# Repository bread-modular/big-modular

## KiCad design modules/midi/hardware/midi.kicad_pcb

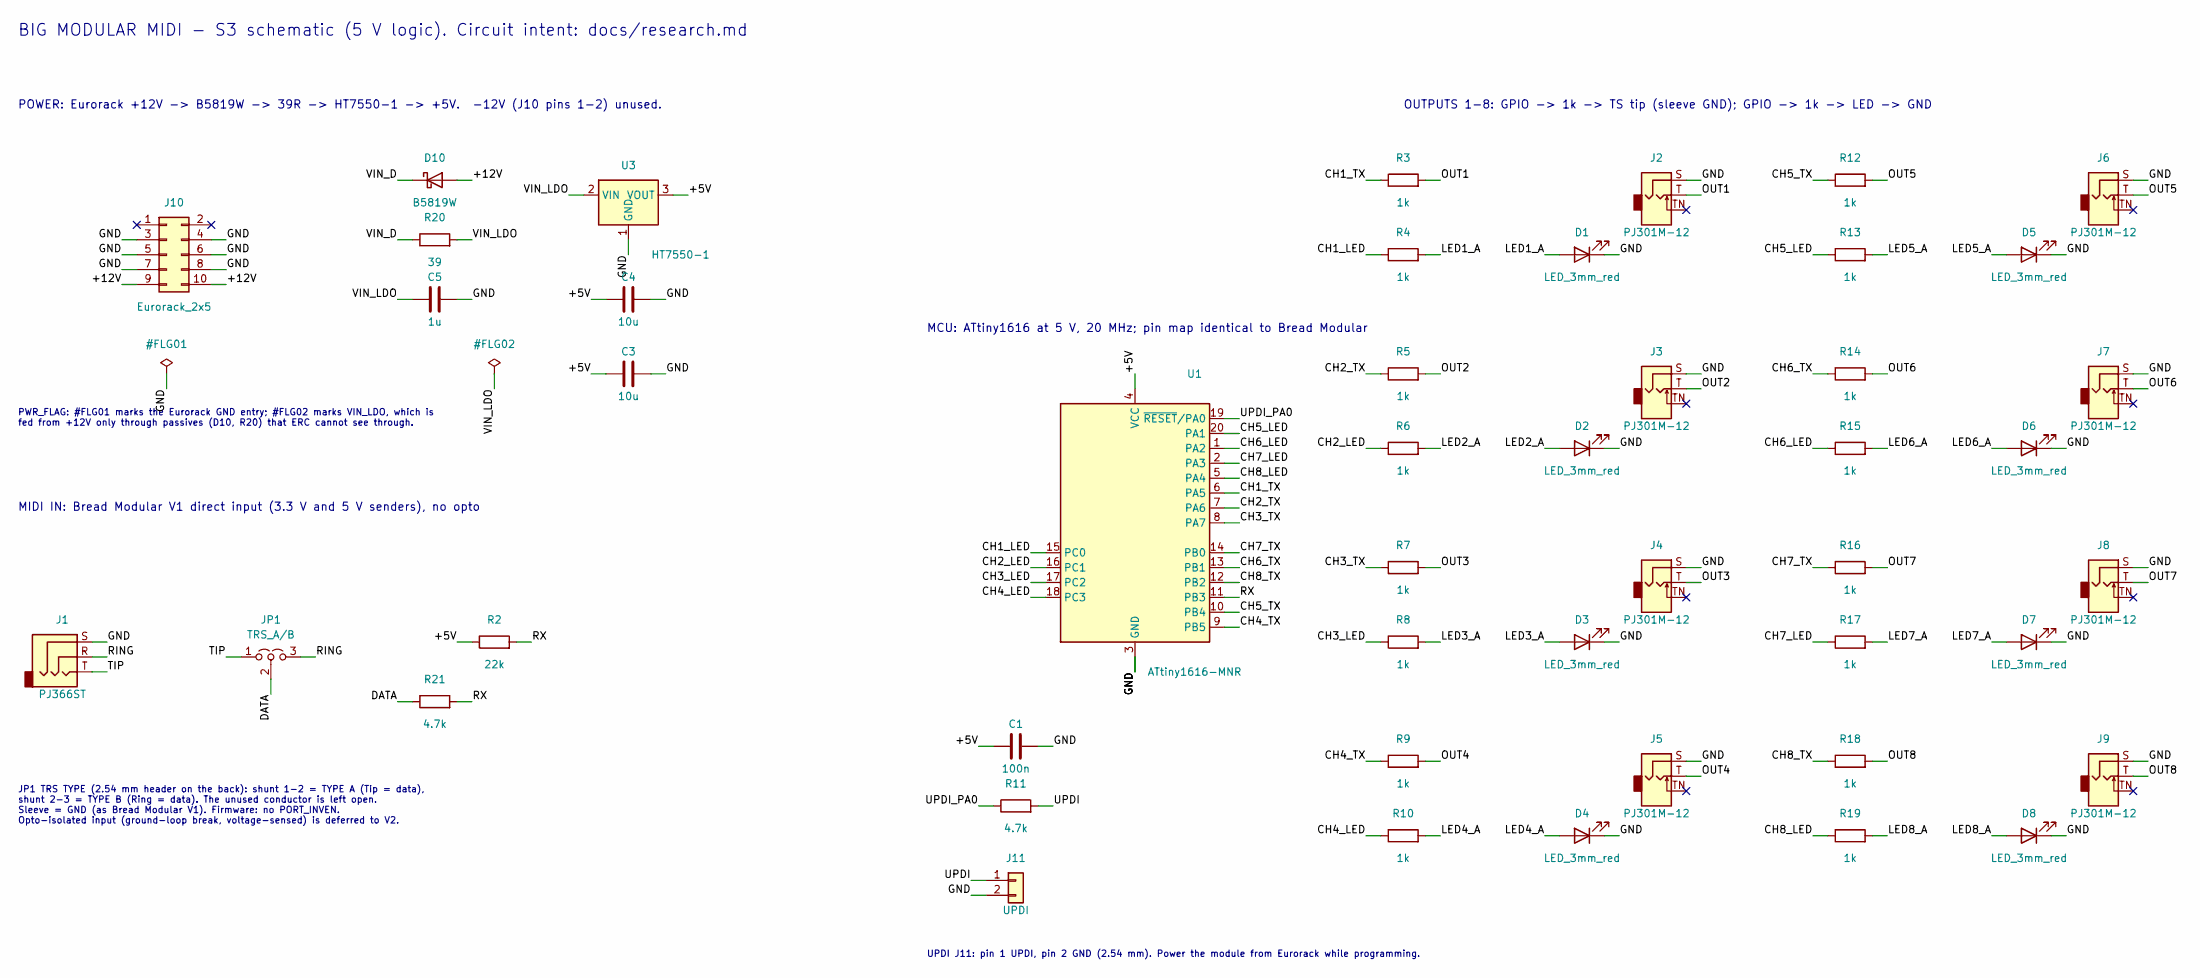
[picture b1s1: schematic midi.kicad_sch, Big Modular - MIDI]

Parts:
C1: 100n; C_0603_1608Metric; Voltage 50V; MPN CC0603KRX7R9BB104; LCSC C14663
C3, C4: 10u; C_0805_2012Metric; Voltage 25V; MPN CL21A106KAYNNNE; LCSC C15850
C5: 1u; C_0805_2012Metric; Voltage 50V; MPN CL21B105KBFNNNE; LCSC C28323
D1, D2, D3, D4, D5, D6, D7, D8: LED_3mm_red; LED_D3.0mm
D10: B5819W; D_SOD-123; MPN B5819W SL; LCSC C8598
J1: PJ366ST; Jack_3.5mm_QingPu_WQP-PJ366ST_Vertical
J2, J3, J4, J5, J6, J7, J8, J9: PJ301M-12; Jack_3.5mm_QingPu_WQP-PJ301M-12_Vertical
J10: Eurorack_2x5; PinHeader_2x05_P2.54mm_Vertical
J11: UPDI; PinHeader_1x02_P2.54mm_Vertical
JP1: TRS_A/B; PinHeader_1x03_P2.54mm_Vertical
R2: 22k; R_0603_1608Metric; MPN 0603WAF2202T5E; LCSC C31850
R3, R4, R5, R6, R7, R8, R9, R10, R12, R13, R14, R15, R16, R17, R18, R19: 1k; R_0603_1608Metric; MPN 0603WAF1001T5E; LCSC C21190
R11, R21: 4.7k; R_0603_1608Metric; MPN 0603WAF4701T5E; LCSC C23162
R20: 39; R_1206_3216Metric; MPN HP06W2F390JT5E; LCSC C414944
U1: ATtiny1616-MNR; VQFN-20-1EP_3x3mm_P0.4mm_EP1.7x1.7mm; MPN ATTINY1616-MNR; LCSC C507118
U3: HT7550-1; SOT-89-3; MPN HT7550-1; LCSC C16106

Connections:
/+5V: C1.1, C3.1, C4.1, R2.1, U1.4 (VCC), U3.3 (VOUT)
/+12V: D10.2 (A), J10.9, J10.10
/CH1_LED: R4.1, U1.15 (PC0)
/CH1_TX: R3.1, U1.6 (PA5)
/CH2_LED: R6.1, U1.16 (PC1)
/CH2_TX: R5.1, U1.7 (PA6)
/CH3_LED: R8.1, U1.17 (PC2)
/CH3_TX: R7.1, U1.8 (PA7)
/CH4_LED: R10.1, U1.18 (PC3)
/CH4_TX: R9.1, U1.9 (PB5)
/CH5_LED: R13.1, U1.20 (PA1)
/CH5_TX: R12.1, U1.10 (PB4)
/CH6_LED: R15.1, U1.1 (PA2)
/CH6_TX: R14.1, U1.13 (PB1)
/CH7_LED: R17.1, U1.2 (PA3)
/CH7_TX: R16.1, U1.14 (PB0)
/CH8_LED: R19.1, U1.5 (PA4)
/CH8_TX: R18.1, U1.12 (PB2)
/DATA: JP1.2 (C), R21.1
/GND: C1.2, C3.2, C4.2, C5.2, D1.1 (K), D2.1 (K), D3.1 (K), D4.1 (K), D5.1 (K), D6.1 (K), D7.1 (K), D8.1 (K), J1.S, J2.S, J3.S, J4.S, J5.S, J6.S, J7.S, J8.S, J9.S, J10.3, J10.4, J10.5, J10.6, J10.7, J10.8, J11.2, U1.3 (GND), U1.21 (GND), U3.1 (GND)
/LED1_A: D1.2 (A), R4.2
/LED2_A: D2.2 (A), R6.2
/LED3_A: D3.2 (A), R8.2
/LED4_A: D4.2 (A), R10.2
/LED5_A: D5.2 (A), R13.2
/LED6_A: D6.2 (A), R15.2
/LED7_A: D7.2 (A), R17.2
/LED8_A: D8.2 (A), R19.2
/OUT1: J2.T, R3.2
/OUT2: J3.T, R5.2
/OUT3: J4.T, R7.2
/OUT4: J5.T, R9.2
/OUT5: J6.T, R12.2
/OUT6: J7.T, R14.2
/OUT7: J8.T, R16.2
/OUT8: J9.T, R18.2
/RING: J1.R, JP1.3 (B)
/RX: R2.2, R21.2, U1.11 (PB3)
/TIP: J1.T, JP1.1 (A)
/UPDI: J11.1, R11.2
/UPDI_PA0: R11.1, U1.19 (~RESET/PA0)
/VIN_D: D10.1 (K), R20.1
/VIN_LDO: C5.1, R20.2, U3.2 (VIN)

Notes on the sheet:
JP1 TRS TYPE (2.54 mm header on the back): shunt 1-2 = TYPE A (Tip = data), shunt 2-3 = TYPE B (Ring = data). The unused conductor is left open. Sleeve = GND (as Bread Modular V1). Firmware: no PORT_INVEN. Opto-isolated input (ground-loop break, voltage-sensed) is deferred to V2.
MIDI IN: Bread Modular V1 direct input (3.3 V and 5 V senders), no opto
OUTPUTS 1-8: GPIO -> 1k -> TS tip (sleeve GND); GPIO -> 1k -> LED -> GND
PWR_FLAG: #FLG01 marks the Eurorack GND entry; #FLG02 marks VIN_LDO, which is fed from +12V only through passives (D10, R20) that ERC cannot see through.
POWER: Eurorack +12V -> B5819W -> 39R -> HT7550-1 -> +5V. -12V (J10 pins 1-2) unused.
BIG MODULAR MIDI - S3 schematic (5 V logic). Circuit intent: docs/research.md
UPDI J11: pin 1 UPDI, pin 2 GND (2.54 mm). Power the module from Eurorack while programming.
MCU: ATtiny1616 at 5 V, 20 MHz; pin map identical to Bread Modular

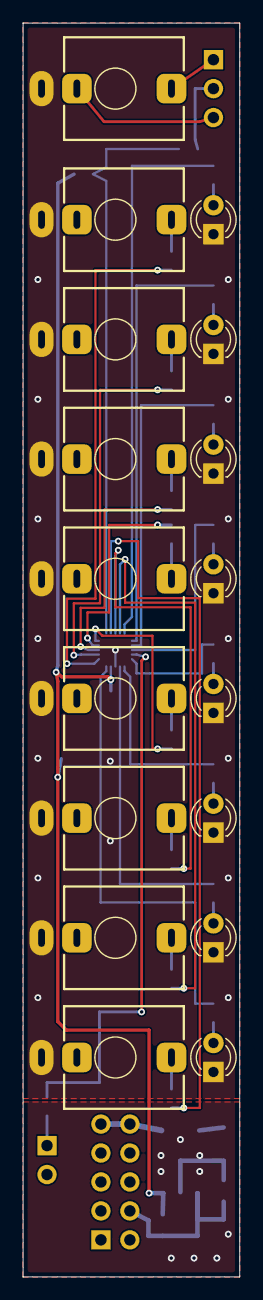
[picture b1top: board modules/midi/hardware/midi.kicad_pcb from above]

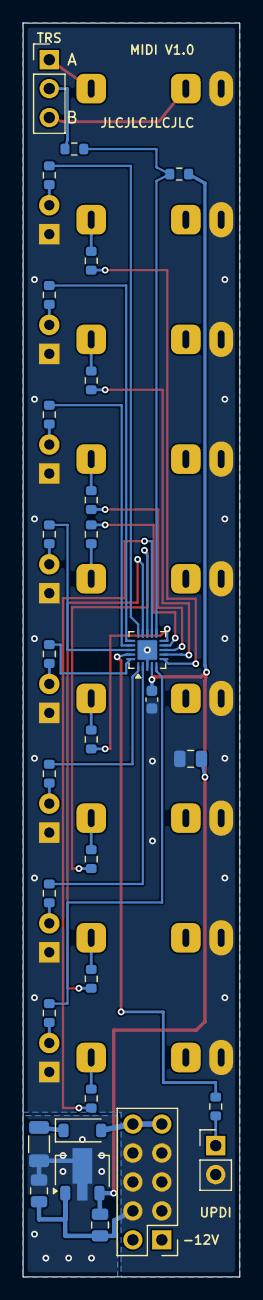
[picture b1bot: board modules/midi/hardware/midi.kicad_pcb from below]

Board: 2 copper layers, 19.0 x 110.0 mm, 47 parts (30 on the bottom side), 43 nets.

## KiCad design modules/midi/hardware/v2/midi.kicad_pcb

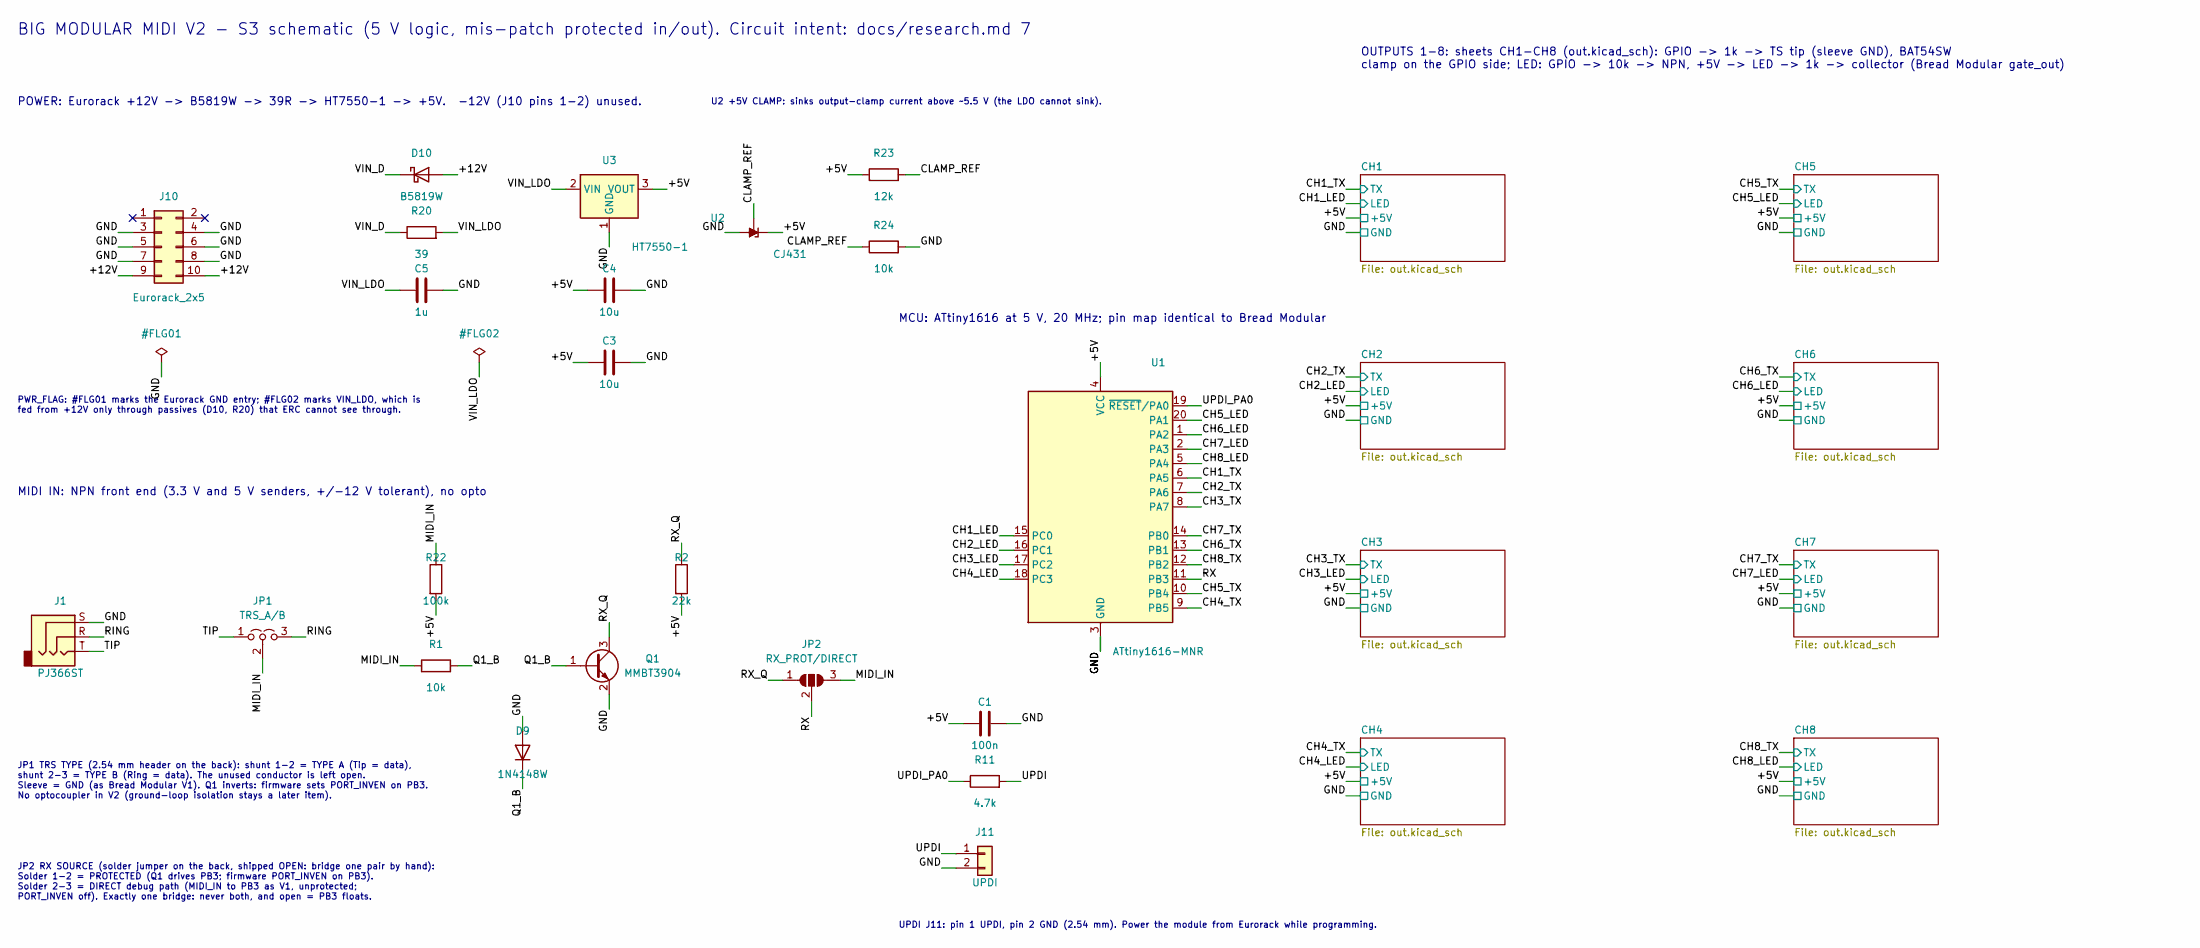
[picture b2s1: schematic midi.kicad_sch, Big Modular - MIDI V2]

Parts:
C1: 100n; C_0603_1608Metric; Voltage 50V; MPN CC0603KRX7R9BB104; LCSC C14663
C3, C4: 10u; C_0805_2012Metric; Voltage 25V; MPN CL21A106KAYNNNE; LCSC C15850
C5: 1u; C_0805_2012Metric; Voltage 50V; MPN CL21B105KBFNNNE; LCSC C28323
D9: 1N4148W; D_SOD-123; MPN 1N4148W; LCSC C81598
D10: B5819W; D_SOD-123; MPN B5819W SL; LCSC C8598
J1: PJ366ST; Jack_3.5mm_QingPu_WQP-PJ366ST_Vertical
J10: Eurorack_2x5; PinHeader_2x05_P2.54mm_Vertical
J11: UPDI; PinHeader_1x02_P2.54mm_Vertical
JP1: TRS_A/B; PinHeader_1x03_P2.54mm_Vertical
JP2: RX_PROT/DIRECT; SolderJumper-3_P1.3mm_Open_RoundedPad1.0x1.5mm
Q1: MMBT3904; SOT-23; MPN MMBT3904(RANGE:100-300); LCSC C20526
R1, R24: 10k; R_0603_1608Metric; MPN 0603WAF1002T5E; LCSC C25804
R2: 22k; R_0603_1608Metric; MPN 0603WAF2202T5E; LCSC C31850
R11: 4.7k; R_0603_1608Metric; MPN 0603WAF4701T5E; LCSC C23162
R20: 39; R_1206_3216Metric; MPN HP06W2F390JT5E; LCSC C414944
R22: 100k; R_0603_1608Metric; MPN 0603WAF1003T5E; LCSC C25803
R23: 12k; R_0603_1608Metric; MPN 0603WAF1202T5E; LCSC C22790
U1: ATtiny1616-MNR; VQFN-20-1EP_3x3mm_P0.4mm_EP1.7x1.7mm; MPN ATTINY1616-MNR; LCSC C507118
U2: CJ431; SOT-23; MPN CJ431; LCSC C3113
U3: HT7550-1; SOT-89-3; MPN HT7550-1; LCSC C16106

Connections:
/+5V: C1.1, C3.1, C4.1, R2.2, R22.2, R23.1, U1.4 (VCC), U2.2 (K), U3.3 (VOUT); also elsewhere on the board
/+12V: D10.2 (A), J10.9, J10.10
/CH1_LED: U1.15 (PC0); also elsewhere on the board
/CH1_TX: U1.6 (PA5); also elsewhere on the board
/CH2_LED: U1.16 (PC1); also elsewhere on the board
/CH2_TX: U1.7 (PA6); also elsewhere on the board
/CH3_LED: U1.17 (PC2); also elsewhere on the board
/CH3_TX: U1.8 (PA7); also elsewhere on the board
/CH4_LED: U1.18 (PC3); also elsewhere on the board
/CH4_TX: U1.9 (PB5); also elsewhere on the board
/CH5_LED: U1.20 (PA1); also elsewhere on the board
/CH5_TX: U1.10 (PB4); also elsewhere on the board
/CH6_LED: U1.1 (PA2); also elsewhere on the board
/CH6_TX: U1.13 (PB1); also elsewhere on the board
/CH7_LED: U1.2 (PA3); also elsewhere on the board
/CH7_TX: U1.14 (PB0); also elsewhere on the board
/CH8_LED: U1.5 (PA4); also elsewhere on the board
/CH8_TX: U1.12 (PB2); also elsewhere on the board
/CLAMP_REF: R23.2, R24.1, U2.1 (REF)
/GND: C1.2, C3.2, C4.2, C5.2, D9.2 (A), J1.S, J10.3, J10.4, J10.5, J10.6, J10.7, J10.8, J11.2, Q1.2 (E), R24.2, U1.3 (GND), U1.21 (GND), U2.3 (A), U3.1 (GND); also elsewhere on the board
/MIDI_IN: JP1.2 (C), JP2.3 (B), R1.1, R22.1
/Q1_B: D9.1 (K), Q1.1 (B), R1.2
/RING: J1.R, JP1.3 (B)
/RX: JP2.2 (C), U1.11 (PB3)
/RX_Q: JP2.1 (A), Q1.3 (C), R2.1
/TIP: J1.T, JP1.1 (A)
/UPDI: J11.1, R11.2
/UPDI_PA0: R11.1, U1.19 (~RESET/PA0)
/VIN_D: D10.1 (K), R20.1
/VIN_LDO: C5.1, R20.2, U3.2 (VIN)

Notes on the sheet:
UPDI J11: pin 1 UPDI, pin 2 GND (2.54 mm). Power the module from Eurorack while programming.
OUTPUTS 1-8: sheets CH1-CH8 (out.kicad_sch): GPIO -> 1k -> TS tip (sleeve GND), BAT54SW clamp on the GPIO side; LED: GPIO -> 10k -> NPN, +5V -> LED -> 1k -> collector (Bread Modular gate_out)
JP1 TRS TYPE (2.54 mm header on the back): shunt 1-2 = TYPE A (Tip = data), shunt 2-3 = TYPE B (Ring = data). The unused conductor is left open. Sleeve = GND (as Bread Modular V1). Q1 inverts: firmware sets PORT_INVEN on PB3. No optocoupler in V2 (ground-loop isolation stays a later item).
MIDI IN: NPN front end (3.3 V and 5 V senders, +/-12 V tolerant), no opto
MCU: ATtiny1616 at 5 V, 20 MHz; pin map identical to Bread Modular
PWR_FLAG: #FLG01 marks the Eurorack GND entry; #FLG02 marks VIN_LDO, which is fed from +12V only through passives (D10, R20) that ERC cannot see through.
POWER: Eurorack +12V -> B5819W -> 39R -> HT7550-1 -> +5V. -12V (J10 pins 1-2) unused.
BIG MODULAR MIDI V2 - S3 schematic (5 V logic, mis-patch protected in/out). Circuit intent: docs/research.md 7
U2 +5V CLAMP: sinks output-clamp current above ~5.5 V (the LDO cannot sink).
JP2 RX SOURCE (solder jumper on the back, shipped OPEN: bridge one pair by hand): Solder 1-2 = PROTECTED (Q1 drives PB3; firmware PORT_INVEN on PB3). Solder 2-3 = DIRECT debug path (MIDI_IN to PB3 as V1, unprotected; PORT_INVEN off). Exactly one bridge: never both, and open = PB3 floats.

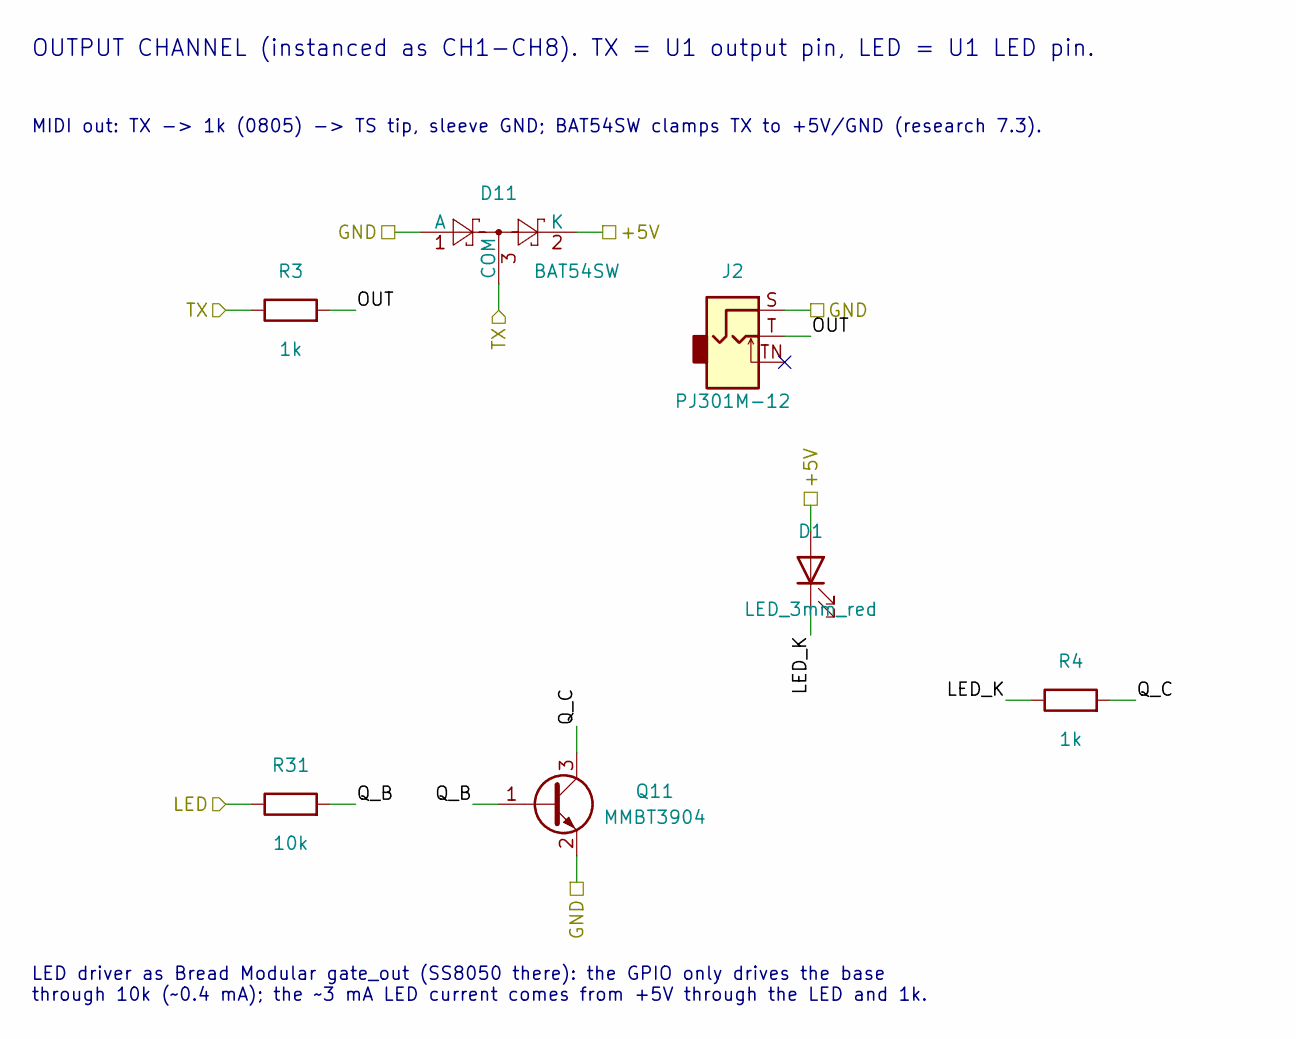
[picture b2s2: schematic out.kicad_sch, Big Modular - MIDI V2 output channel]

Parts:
D1: LED_3mm_red; LED_D3.0mm
D11: BAT54SW; SOT-323_SC-70; MPN BAT54SWT1G; LCSC C78260
J2: PJ301M-12; Jack_3.5mm_QingPu_WQP-PJ301M-12_Vertical
Q11: MMBT3904; SOT-23; MPN MMBT3904(RANGE:100-300); LCSC C20526
R3: 1k; R_0805_2012Metric; MPN 0805W8F1001T5E; LCSC C17513
R4: 1k; R_0603_1608Metric; MPN 0603WAF1001T5E; LCSC C21190
R31: 10k; R_0603_1608Metric; MPN 0603WAF1002T5E; LCSC C25804

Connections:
/+5V: D1.2 (A), D11.2 (K); also elsewhere on the board
/CH1/LED_K: D1.1 (K), R4.1
/CH1/OUT: J2.T, R3.2
/CH1/Q_B: Q11.1 (B), R31.2
/CH1/Q_C: Q11.3 (C), R4.2
/CH1_LED: R31.1; also elsewhere on the board
/CH1_TX: D11.3 (COM), R3.1; also elsewhere on the board
/GND: D11.1 (A), J2.S, Q11.2 (E); also elsewhere on the board

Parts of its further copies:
D2, D3, D4, D5, D6, D7, D8: LED_3mm_red; LED_D3.0mm
D12, D13, D14, D15, D16, D17, D18: BAT54SW; SOT-323_SC-70; MPN BAT54SWT1G; LCSC C78260
J3, J4, J5, J6, J7, J8, J9: PJ301M-12; Jack_3.5mm_QingPu_WQP-PJ301M-12_Vertical
Q12, Q13, Q14, Q15, Q16, Q17, Q18: MMBT3904; SOT-23; MPN MMBT3904(RANGE:100-300); LCSC C20526
R5, R7, R9, R12, R14, R16, R18: 1k; R_0805_2012Metric; MPN 0805W8F1001T5E; LCSC C17513
R6, R8, R10, R13, R15, R17, R19: 1k; R_0603_1608Metric; MPN 0603WAF1001T5E; LCSC C21190
R32, R33, R34, R35, R36, R37, R38: 10k; R_0603_1608Metric; MPN 0603WAF1002T5E; LCSC C25804

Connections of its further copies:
/+5V: D2.2 (A), D3.2 (A), D4.2 (A), D5.2 (A), D6.2 (A), D7.2 (A), D8.2 (A), D12.2 (K), D13.2 (K), D14.2 (K), D15.2 (K), D16.2 (K), D17.2 (K), D18.2 (K); also elsewhere on the board
/CH2/LED_K: D2.1 (K), R6.1
/CH2/OUT: J3.T, R5.2
/CH2/Q_B: Q12.1 (B), R32.2
/CH2/Q_C: Q12.3 (C), R6.2
/CH2_LED: R32.1; also elsewhere on the board
/CH2_TX: D12.3 (COM), R5.1; also elsewhere on the board
/CH3/LED_K: D3.1 (K), R8.1
/CH3/OUT: J4.T, R7.2
/CH3/Q_B: Q13.1 (B), R33.2
/CH3/Q_C: Q13.3 (C), R8.2
/CH3_LED: R33.1; also elsewhere on the board
/CH3_TX: D13.3 (COM), R7.1; also elsewhere on the board
/CH4/LED_K: D4.1 (K), R10.1
/CH4/OUT: J5.T, R9.2
/CH4/Q_B: Q14.1 (B), R34.2
/CH4/Q_C: Q14.3 (C), R10.2
/CH4_LED: R34.1; also elsewhere on the board
/CH4_TX: D14.3 (COM), R9.1; also elsewhere on the board
/CH5/LED_K: D5.1 (K), R13.1
/CH5/OUT: J6.T, R12.2
/CH5/Q_B: Q15.1 (B), R35.2
/CH5/Q_C: Q15.3 (C), R13.2
/CH5_LED: R35.1; also elsewhere on the board
/CH5_TX: D15.3 (COM), R12.1; also elsewhere on the board
/CH6/LED_K: D6.1 (K), R15.1
/CH6/OUT: J7.T, R14.2
/CH6/Q_B: Q16.1 (B), R36.2
/CH6/Q_C: Q16.3 (C), R15.2
/CH6_LED: R36.1; also elsewhere on the board
/CH6_TX: D16.3 (COM), R14.1; also elsewhere on the board
/CH7/LED_K: D7.1 (K), R17.1
/CH7/OUT: J8.T, R16.2
/CH7/Q_B: Q17.1 (B), R37.2
/CH7/Q_C: Q17.3 (C), R17.2
/CH7_LED: R37.1; also elsewhere on the board
/CH7_TX: D17.3 (COM), R16.1; also elsewhere on the board
/CH8/LED_K: D8.1 (K), R19.1
/CH8/OUT: J9.T, R18.2
/CH8/Q_B: Q18.1 (B), R38.2
/CH8/Q_C: Q18.3 (C), R19.2
/CH8_LED: R38.1; also elsewhere on the board
/CH8_TX: D18.3 (COM), R18.1; also elsewhere on the board
/GND: D12.1 (A), D13.1 (A), D14.1 (A), D15.1 (A), D16.1 (A), D17.1 (A), D18.1 (A), J3.S, J4.S, J5.S, J6.S, J7.S, J8.S, J9.S, Q12.2 (E), Q13.2 (E), Q14.2 (E), Q15.2 (E), Q16.2 (E), Q17.2 (E), Q18.2 (E); also elsewhere on the board

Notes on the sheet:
OUTPUT CHANNEL (instanced as CH1-CH8). TX = U1 output pin, LED = U1 LED pin.
MIDI out: TX -> 1k (0805) -> TS tip, sleeve GND; BAT54SW clamps TX to +5V/GND (research 7.3).
LED driver as Bread Modular gate_out (SS8050 there): the GPIO only drives the base through 10k (~0.4 mA); the ~3 mA LED current comes from +5V through the LED and 1k.

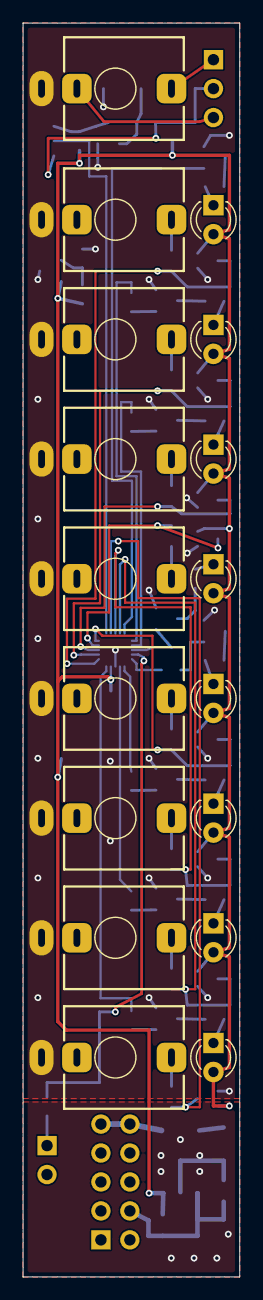
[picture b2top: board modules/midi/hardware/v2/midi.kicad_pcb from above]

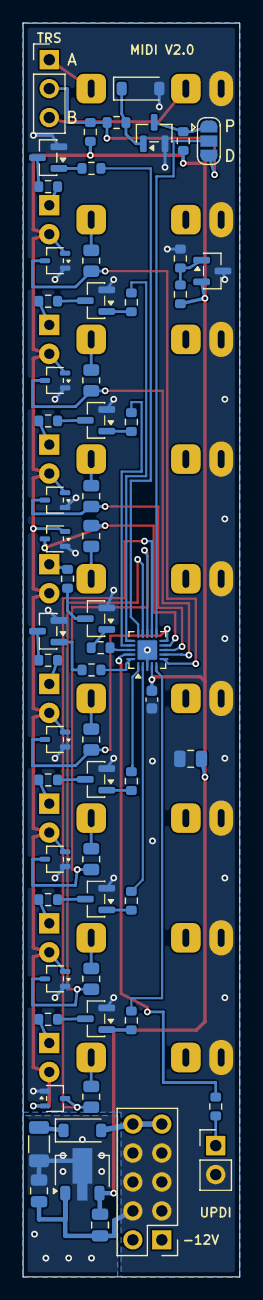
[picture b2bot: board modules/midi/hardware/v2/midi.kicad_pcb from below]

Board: 2 copper layers, 19.0 x 110.0 mm, 78 parts (61 on the bottom side), 62 nets.

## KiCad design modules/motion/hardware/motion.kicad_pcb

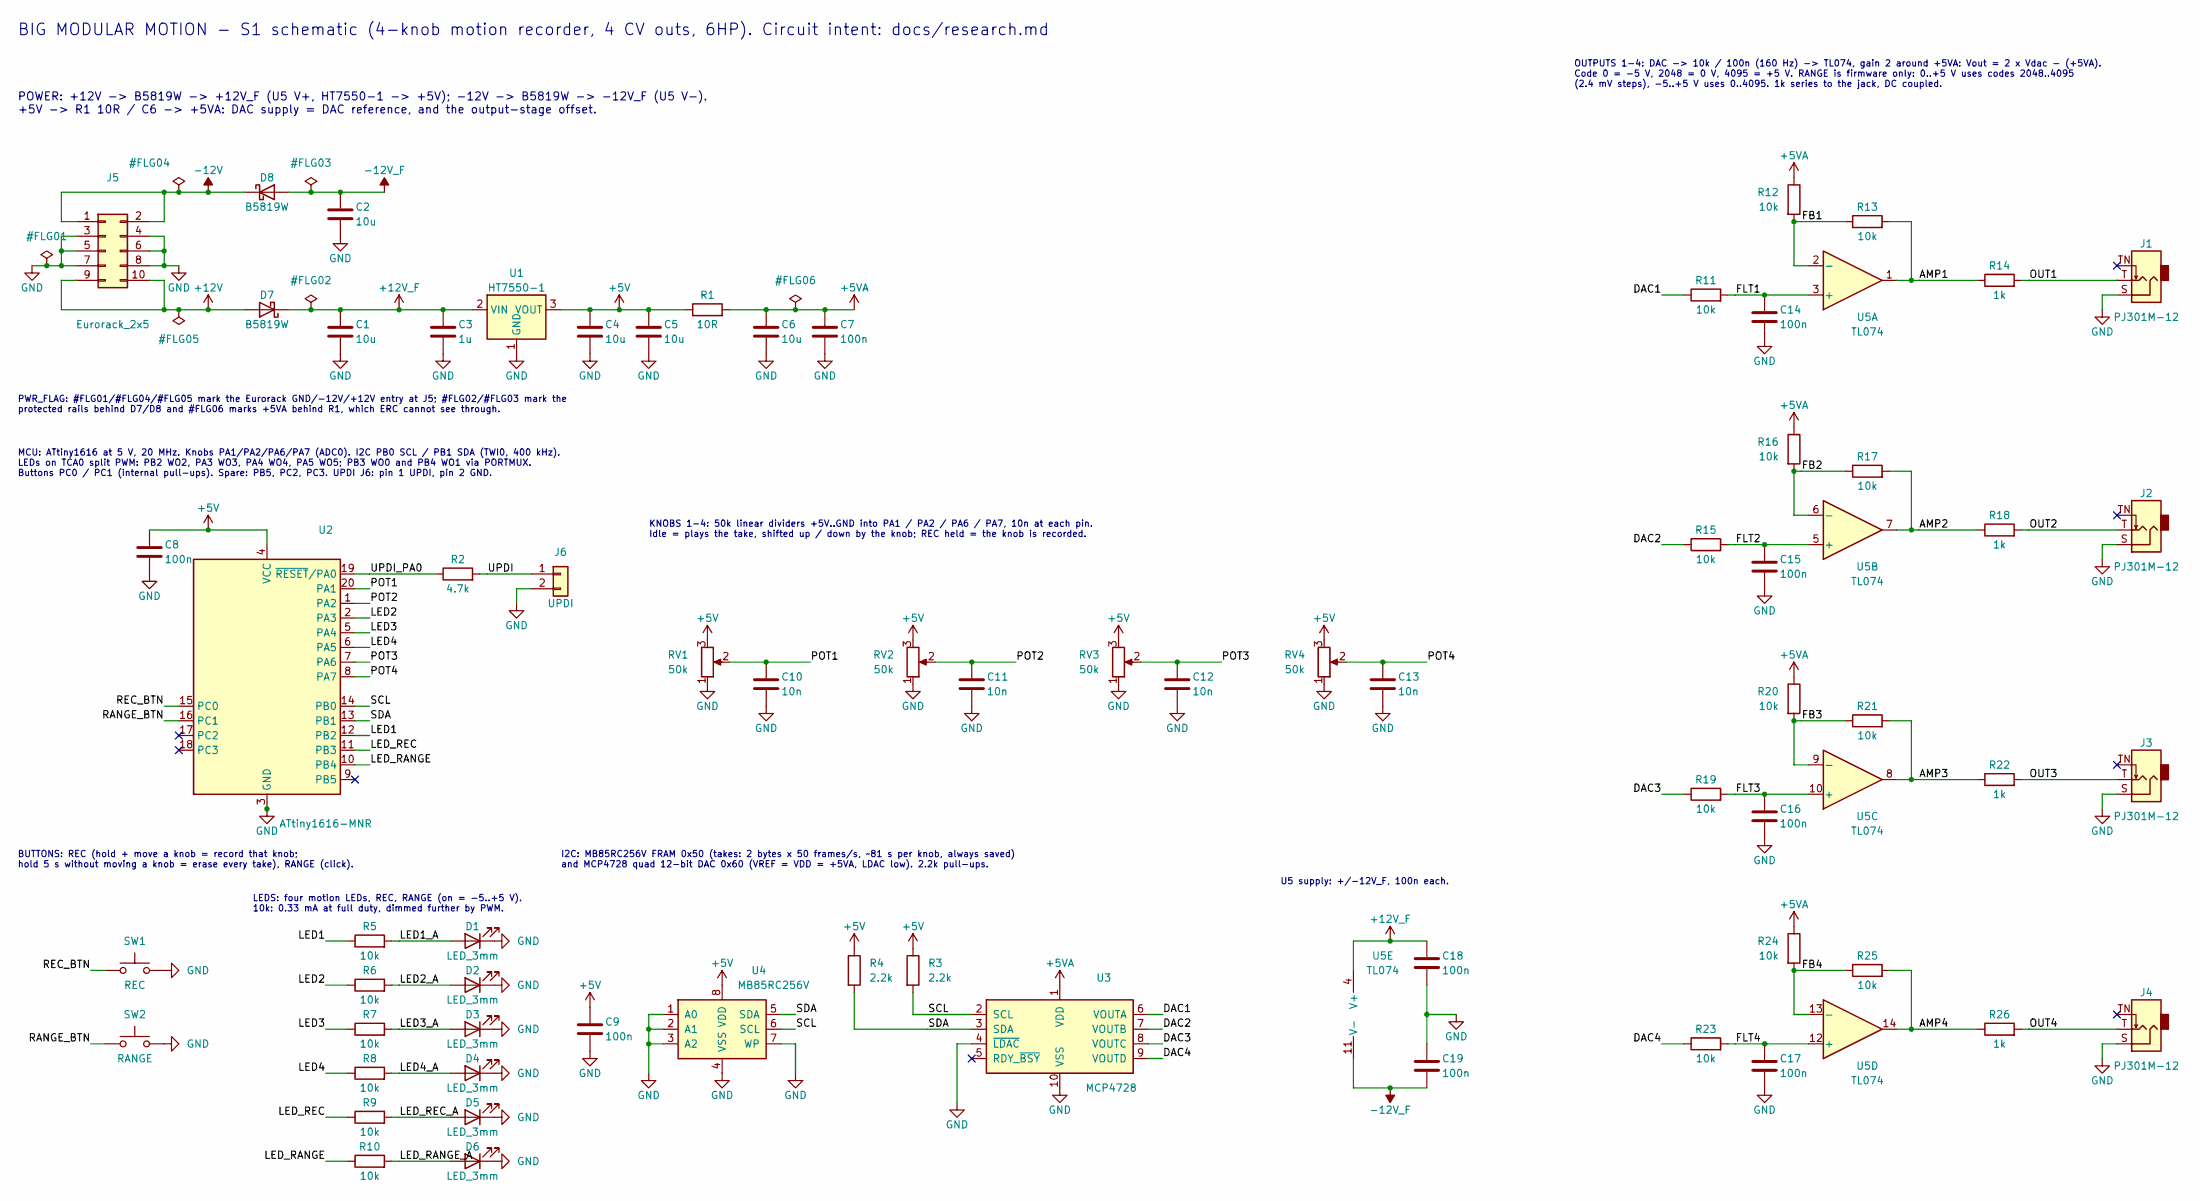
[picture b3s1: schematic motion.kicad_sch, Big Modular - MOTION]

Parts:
C1, C2, C4, C5, C6: 10u; C_0805_2012Metric; Voltage 25V; MPN CL21A106KAYNNNE; LCSC C15850
C3: 1u; C_0805_2012Metric; Voltage 50V; MPN CL21B105KBFNNNE; LCSC C28323
C7, C8, C9, C14, C15, C16, C17, C18, C19: 100n; C_0603_1608Metric; Voltage 50V; MPN CC0603KRX7R9BB104; LCSC C14663
C10, C11, C12, C13: 10n; C_0603_1608Metric; Voltage 50V; MPN 0603B103K500NT; LCSC C57112
D1, D2, D3, D4, D5, D6: LED_3mm; LED_D3.0mm
D7, D8: B5819W; D_SOD-123; MPN B5819W SL; LCSC C8598
J1, J2, J3, J4: PJ301M-12; Jack_3.5mm_QingPu_WQP-PJ301M-12_Vertical
J5: Eurorack_2x5; PinHeader_2x05_P2.54mm_Vertical
J6: UPDI; PinHeader_1x02_P2.54mm_Vertical
R1: 10R; R_0603_1608Metric; MPN 0603WAF100JT5E; LCSC C22859
R2: 4.7k; R_0603_1608Metric; MPN 0603WAF4701T5E; LCSC C23162
R3, R4: 2.2k; R_0603_1608Metric; MPN 0603WAF2201T5E; LCSC C4190
R5, R6, R7, R8, R9, R10, R11, R12, R13, R15, R16, R17, R19, R20, R21, R23, R24, R25: 10k; R_0603_1608Metric; MPN 0603WAF1002T5E; LCSC C25804
R14, R18, R22, R26: 1k; R_1206_3216Metric; MPN ESR18EZPF1001; LCSC C2074262
RV1, RV2, RV3, RV4: 50k; Potentiometer_RV09
SW1: REC; SW_PUSH_6mm_H7.3mm; MPN 6x6x7 mm THT tact switch, 4 pins (gener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
SW2: RANGE; SW_PUSH_6mm_H7.3mm; MPN 6x6x7 mm THT tact switch, 4 pins (gener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
U1: HT7550-1; SOT-89-3; MPN HT7550-1; LCSC C16106
U2: ATtiny1616-MNR; VQFN-20-1EP_3x3mm_P0.4mm_EP1.7x1.7mm; MPN ATTINY1616-MNR; LCSC C507118
U3: MCP4728; TSSOP-10_3x3mm_P0.5mm; MPN MCP4728T-E/UN; LCSC C478093
U4: MB85RC256V; SOIC-8_3.9x4.9mm_P1.27mm; MPN MB85RC256VPNF-G-AMERE2; LCSC C45273903
U5: TL074; SOIC-14_3.9x8.7mm_P1.27mm; MPN TL074CDR; LCSC C12594

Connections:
+5V: C4.1, C5.1, C8.1, C9.1, R1.1, R3.1, R4.1, RV1.3, RV2.3, RV3.3, RV4.3, U1.3 (VOUT), U2.4 (VCC), U4.8 (VDD)
+5VA: C6.1, C7.1, R1.2, R12.1, R16.1, R20.1, R24.1, U3.1 (VDD)
+12V: D7.2 (A), J5.9, J5.10
+12V_F: C1.1, C3.1, C18.1, D7.1 (K), U1.2 (VIN), U5.4 (V+)
-12V: D8.1 (K), J5.1, J5.2
-12V_F: C2.2, C19.2, D8.2 (A), U5.11 (V-)
/AMP1: R13.2, R14.1, U5.1
/AMP2: R17.2, R18.1, U5.7
/AMP3: R21.2, R22.1, U5.8
/AMP4: R25.2, R26.1, U5.14
/DAC1: R11.1, U3.6 (VOUTA)
/DAC2: R15.1, U3.7 (VOUTB)
/DAC3: R19.1, U3.8 (VOUTC)
/DAC4: R23.1, U3.9 (VOUTD)
/FB1: R12.2, R13.1, U5.2 (-)
/FB2: R16.2, R17.1, U5.6 (-)
/FB3: R20.2, R21.1, U5.9 (-)
/FB4: R24.2, R25.1, U5.13 (-)
/FLT1: C14.1, R11.2, U5.3 (+)
/FLT2: C15.1, R15.2, U5.5 (+)
/FLT3: C16.1, R19.2, U5.10 (+)
/FLT4: C17.1, R23.2, U5.12 (+)
/LED1: R5.1, U2.12 (PB2)
/LED1_A: D1.2 (A), R5.2
/LED2: R6.1, U2.2 (PA3)
/LED2_A: D2.2 (A), R6.2
/LED3: R7.1, U2.5 (PA4)
/LED3_A: D3.2 (A), R7.2
/LED4: R8.1, U2.6 (PA5)
/LED4_A: D4.2 (A), R8.2
/LED_RANGE: R10.1, U2.10 (PB4)
/LED_RANGE_A: D6.2 (A), R10.2
/LED_REC: R9.1, U2.11 (PB3)
/LED_REC_A: D5.2 (A), R9.2
/OUT1: J1.T, R14.2
/OUT2: J2.T, R18.2
/OUT3: J3.T, R22.2
/OUT4: J4.T, R26.2
/POT1: C10.1, RV1.2, U2.20 (PA1)
/POT2: C11.1, RV2.2, U2.1 (PA2)
/POT3: C12.1, RV3.2, U2.7 (PA6)
/POT4: C13.1, RV4.2, U2.8 (PA7)
/RANGE_BTN: SW2.1, U2.16 (PC1)
/REC_BTN: SW1.1, U2.15 (PC0)
/SCL: R3.2, U2.14 (PB0), U3.2 (SCL), U4.6 (SCL)
/SDA: R4.2, U2.13 (PB1), U3.3 (SDA), U4.5 (SDA)
/UPDI: J6.1, R2.2
/UPDI_PA0: R2.1, U2.19 (~RESET/PA0)
GND: C1.2, C2.1, C3.2, C4.2, C5.2, C6.2, C7.2, C8.2, C9.2, C10.2, C11.2, C12.2, C13.2, C14.2, C15.2, C16.2, C17.2, C18.2, C19.1, D1.1 (K), D2.1 (K), D3.1 (K), D4.1 (K), D5.1 (K), D6.1 (K), J1.S, J2.S, J3.S, J4.S, J5.3, J5.4, J5.5, J5.6, J5.7, J5.8, J6.2, RV1.1, RV2.1, RV3.1, RV4.1, SW1.2, SW2.2, U1.1 (GND), U2.3 (GND), U2.21 (GND), U3.4 (~LDAC), U3.10 (VSS), U4.1 (A0), U4.2 (A1), U4.3 (A2), U4.4 (VSS), U4.7 (WP)

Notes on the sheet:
LEDS: four motion LEDs, REC, RANGE (on = -5..+5 V). 10k: 0.33 mA at full duty, dimmed further by PWM.
KNOBS 1-4: 50k linear dividers +5V..GND into PA1 / PA2 / PA6 / PA7, 10n at each pin. Idle = plays the take, shifted up / down by the knob; REC held = the knob is recorded.
U5 supply: +/-12V_F, 100n each.
OUTPUTS 1-4: DAC -> 10k / 100n (160 Hz) -> TL074, gain 2 around +5VA: Vout = 2 x Vdac - (+5VA). Code 0 = -5 V, 2048 = 0 V, 4095 = +5 V. RANGE is firmware only: 0..+5 V uses codes 2048..4095 (2.4 mV steps), -5..+5 V uses 0..4095. 1k series to the jack, DC coupled.
BUTTONS: REC (hold + move a knob = record that knob; hold 5 s without moving a knob = erase every take), RANGE (click).
I2C: MB85RC256V FRAM 0x50 (takes: 2 bytes x 50 frames/s, ~81 s per knob, always saved) and MCP4728 quad 12-bit DAC 0x60 (VREF = VDD = +5VA, LDAC low). 2.2k pull-ups.
POWER: +12V -> B5819W -> +12V_F (U5 V+, HT7550-1 -> +5V); -12V -> B5819W -> -12V_F (U5 V-). +5V -> R1 10R / C6 -> +5VA: DAC supply = DAC reference, and the output-stage offset.
BIG MODULAR MOTION - S1 schematic (4-knob motion recorder, 4 CV outs, 6HP). Circuit intent: docs/research.md
PWR_FLAG: #FLG01/#FLG04/#FLG05 mark the Eurorack GND/-12V/+12V entry at J5; #FLG02/#FLG03 mark the protected rails behind D7/D8 and #FLG06 marks +5VA behind R1, which ERC cannot see through.
MCU: ATtiny1616 at 5 V, 20 MHz. Knobs PA1/PA2/PA6/PA7 (ADC0). I2C PB0 SCL / PB1 SDA (TWI0, 400 kHz). LEDs on TCA0 split PWM: PB2 WO2, PA3 WO3, PA4 WO4, PA5 WO5; PB3 WO0 and PB4 WO1 via PORTMUX. Buttons PC0 / PC1 (internal pull-ups). Spare: PB5, PC2, PC3. UPDI J6: pin 1 UPDI, pin 2 GND.

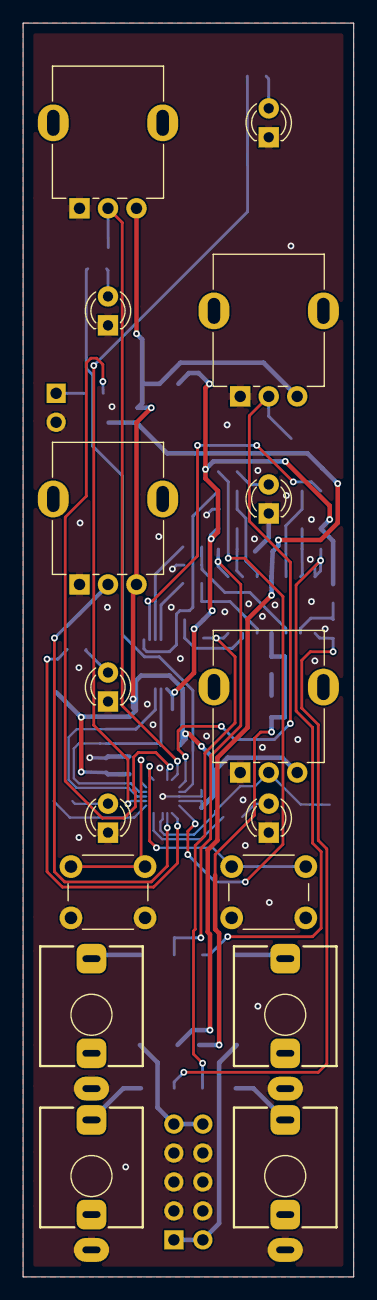
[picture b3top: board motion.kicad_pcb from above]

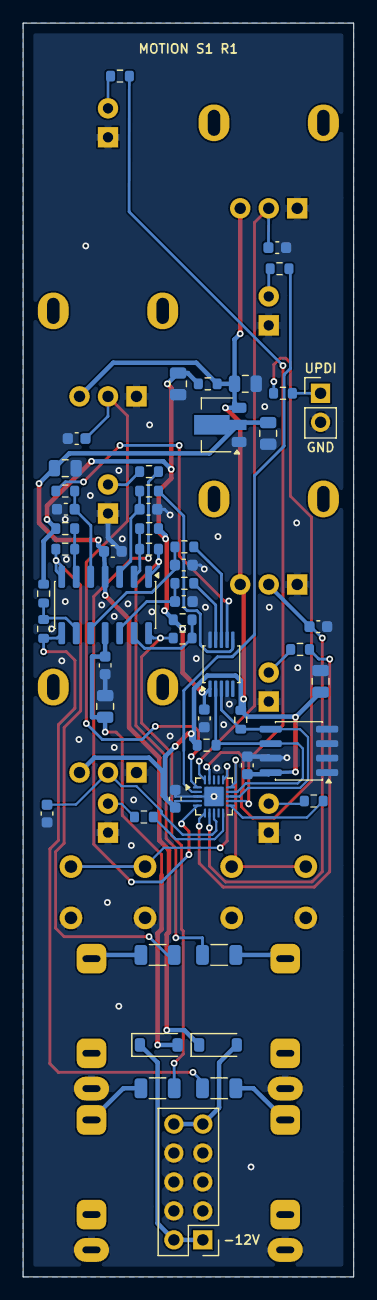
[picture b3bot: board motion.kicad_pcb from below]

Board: 2 copper layers, 29.0 x 110.0 mm, 70 parts (54 on the bottom side), 49 nets.
